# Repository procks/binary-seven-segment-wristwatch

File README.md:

# binary-seven-segment-wristwatch
A minimalist binary wristwatch that tells time using a 7-segment display

[Video](https://www.youtube.com/watch?v=ZBKZWdPcJMU)

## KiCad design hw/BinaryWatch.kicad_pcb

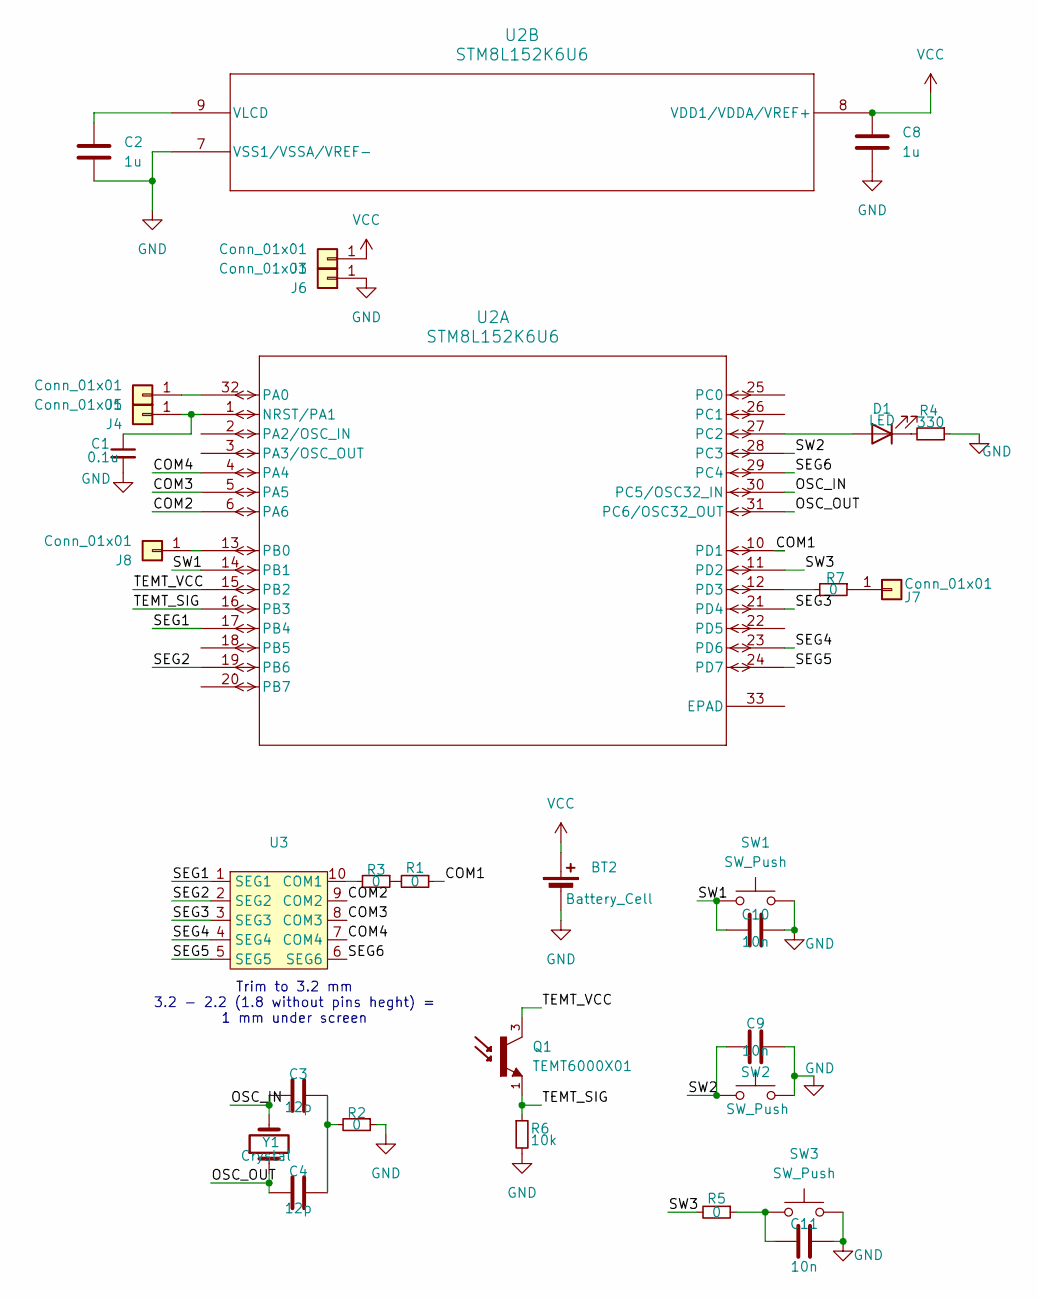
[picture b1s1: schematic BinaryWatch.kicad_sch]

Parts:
BT2: Battery_Cell; BatteryHolder_MYOUNG_BS-07-A1BJ001_CR2032
C1: 0.1u; C_0603_1608Metric
C2: 1u; C_0603_1608Metric
C3, C4: 12p; Fuse_0402_1005Metric
C8: 1u; Fuse_0402_1005Metric
C9, C10, C11: 10n; Fuse_0402_1005Metric
D1: LED; LED_0603_1608Metric
J3, J4, J5, J6, J7, J8: Conn_01x01; SolderWirePad_1x01_SMD_1x2mm
Q1: TEMT6000X01; TRANS_TEMT6000X01; PARTREV 1.9
R1, R2, R3, R5: 0; R_0603_1608Metric
R4: 330; R_0402_1005Metric
R6: 10k; R_0402_1005Metric
R7: 0; R_0402_1005Metric
SW1, SW2: SW_Push; SW_SPST_EVQP7A
SW3: SW_Push; SW_Push_SPST_NO_Alps_SKRK
U2: STM8L152K6U6; UFQFPN32-5x5mm-L
U3: 3SegLCD10Pin
Y1: Crystal; Crystal_SMD_2012-2Pin_2.0x1.2mm

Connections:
/COM1: R1.1, U2.10 (PD1)
/COM2: U2.6 (PA6), U3.9 (COM2)
/COM3: U2.5 (PA5), U3.8 (COM3)
/COM4: U2.4 (PA4), U3.7 (COM4)
/OSC_IN: C3.2, U2.30 (PC5/OSC32_IN), Y1.2
/OSC_OUT: C4.1, U2.31 (PC6/OSC32_OUT), Y1.1
/SEG1: U2.17 (PB4), U3.1 (SEG1)
/SEG2: U2.19 (PB6), U3.2 (SEG2)
/SEG3: U2.21 (PD4), U3.3 (SEG3)
/SEG4: U2.23 (PD6), U3.4 (SEG4)
/SEG5: U2.24 (PD7), U3.5 (SEG5)
/SEG6: U2.29 (PC4), U3.6 (SEG6)
/SW1: C10.1, SW1.1, U2.14 (PB1)
/SW2: C9.1, SW2.1, U2.28 (PC3)
/SW3: R5.2, U2.11 (PD2)
/TEMT_SIG: Q1.1, R6.1, U2.16 (PB3)
/TEMT_VCC: Q1.3, U2.15 (PB2)
GND: BT2.2 (-), C1.2, C2.2, C8.1, C9.2, C10.2, C11.2, J6.1, R2.1, R4.1, R6.2, SW1.2, SW2.2, SW3.2, U2.7 (VSS1/VSSA/VREF-)
unnamed: C3.1, C4.2, R2.2
unnamed: C11.1, R5.1, SW3.1
unnamed: D1.2 (A), U2.27 (PC2)
unnamed: D1.1 (K), R4.2
unnamed: C1.1, J4.1, U2.1 (NRST/PA1)
unnamed: J5.1, U2.32 (PA0)
unnamed: J7.1, R7.1
unnamed: J8.1, U2.13 (PB0)
unnamed: R1.2, R3.1
unnamed: R7.2, U2.12 (PD3)
unnamed: C2.1, U2.9 (VLCD)
unnamed: R3.2, U3.10 (COM1)
VCC: BT2.1 (+), C8.2, J3.1, U2.8 (VDD1/VDDA/VREF+)

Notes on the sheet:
Trim to 3.2 mm 3.2 - 2.2 (1.8 without pins heght) = 1 mm under screen

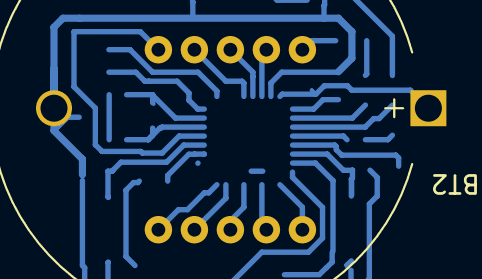
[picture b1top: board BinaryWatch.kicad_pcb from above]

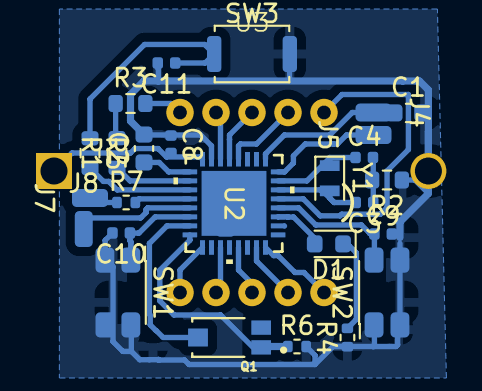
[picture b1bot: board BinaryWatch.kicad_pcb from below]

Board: 2 copper layers, 28 parts (27 on the bottom side), 31 nets.

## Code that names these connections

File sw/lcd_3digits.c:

#include "lcd_3digits.h"

void setDigitSegments(const uint8_t active[7], uint8_t position);

#define DIGIT_N 13
const uint8_t numberSegments[DIGIT_N][7] = {
    // Segments for digits 0-9 (A, B, C, D, E, F, G)
    {1,1,1,1,1,1,0}, // 0
    {0,1,1,0,0,0,0}, // 1
    {1,1,0,1,1,0,1}, // 2
    {1,1,1,1,0,0,1}, // 3
    {0,1,1,0,0,1,1}, // 4
    {1,0,1,1,0,1,1}, // 5
    {1,0,1,1,1,1,1}, // 6
    {1,1,1,0,0,0,0}, // 7
    {1,1,1,1,1,1,1}, // 8
    {1,1,1,1,0,1,1}, // 9
    {1,1,1,1,1,0,0}, // 10
    {0,1,1,0,0,1,0}, // 11
    {1,1,0,1,1,1,1}, // 12
};

const uint8_t emptySegments[DIGIT_N] = {0, 0, 0, 0, 0, 0, 0};  // empty
const uint8_t bitZeroSegments[DIGIT_N] = {0, 0, 0, 0, 0, 0, 1};  // -

static uint8_t activeBits[7];

const uint8_t digit0Segments[7][2] = {
  {2, 0x20}, //A
  {6, 0x02}, //B
  {9, 0x20}, //C
  {13, 0x10}, //D
  {10, 0x01}, //E
  {3, 0x01}, //F
  {6, 0x10}, //G
};

const uint8_t digit1Segments[7][2] = {
  {2, 0x04}, //A
  {5, 0x40}, //B
  {9, 0x04}, //C
  {13, 0x01}, //D
  {9, 0x10}, //E
  {2, 0x10}, //F
  {6, 0x01}, //G
};

const uint8_t digit2Segments[7][2] = {
  {1, 0x40}, //A
  {5, 0x04}, //B
  {8, 0x40}, //C
  {12, 0x10}, //D
  {9, 0x01}, //E
  {2, 0x01}, //F
  {5, 0x10}, //G
};

//Seg1 PB4 SEG14
//Seg2 PB6 SEG16
//Seg3 PD4 SEG18
//Seg4 PD6 SEG20
//Seg5 PD7 SEG21
//Seg6 PC4 SEG24
  
// 28 bit
//example segment 14 com 1: 1 * 28 + 14 = 42;  RAM[42 / 8] = 1 << 42 % 8  //   LCD->RAM[5] |= 0x04
// https://pl.kotl.in/D8QqgNEhd
// https://pl.kotl.in/o2Y2ADsXu
//    val segments = listOf(14, 16, 18, 20, 21, 24)
//    segments.forEach { seg ->
//        for (com in 0..3) {
//                val bitsn = com * 28 + seg
//                val ramIndex = bitsn / 8
//                val bit = bitsn % 8
//                val mask = 1 shl bit
//                //println("LCD->RAM[$ramIndex] |= 0x${mask.toString(16).padStart(2, '0').uppercase()}; // SEG$seg COM$com")
//                println("{$ramIndex, 0x${mask.toString(16).padStart(2, '0').uppercase()}},")
//        }
//    }

//LCD->RAM[1] |= 0x40; // SEG14 COM0 // 3A
//LCD->RAM[5] |= 0x04; // SEG14 COM1 // 3B
//LCD->RAM[8] |= 0x40; // SEG14 COM2 // 3C
////LCD->RAM[12] |= 0x04; // SEG14 COM3 // nc
//LCD->RAM[2] |= 0x01; // SEG16 COM0 // 3F
//LCD->RAM[5] |= 0x10; // SEG16 COM1 // 3G
//LCD->RAM[9] |= 0x01; // SEG16 COM2 // 3E
//LCD->RAM[12] |= 0x10; // SEG16 COM3 // 3D
    
//LCD->RAM[2] |= 0x04; // SEG18 COM0 // 2A
//LCD->RAM[5] |= 0x40; // SEG18 COM1 // 2B
//LCD->RAM[9] |= 0x04; // SEG18 COM2 // 2C
////LCD->RAM[12] |= 0x40; // SEG18 COM3 // nc
//LCD->RAM[2] |= 0x10; // SEG20 COM0 // 2F
//LCD->RAM[6] |= 0x01; // SEG20 COM1 // 2G
//LCD->RAM[9] |= 0x10; // SEG20 COM2 // 2E
//LCD->RAM[13] |= 0x01; // SEG20 COM3 // 2D
    
//LCD->RAM[2] |= 0x20; // SEG21 COM0 // 1A
//LCD->RAM[6] |= 0x02; // SEG21 COM1 // 1B
//LCD->RAM[9] |= 0x20; // SEG21 COM2 // 1C
////LCD->RAM[13] |= 0x02; // SEG21 COM3 // nc
//LCD->RAM[3] |= 0x01; // SEG24 COM0 // 1F
//LCD->RAM[6] |= 0x10; // SEG24 COM1 // 1G
//LCD->RAM[10] |= 0x01; // SEG24 COM2 // 1E
//LCD->RAM[13] |= 0x10; // SEG24 COM3 // 1D

const uint8_t *digitSegmentMappings[] = {
    (const uint8_t *)digit0Segments,
    (const uint8_t *)digit1Segments,
    (const uint8_t *)digit2Segments
};

void setDigitSegments(const uint8_t active[7], uint8_t position) {
    const uint8_t (*segments)[2] = (const uint8_t (*)[2])digitSegmentMappings[position];

    for (int i = 0; i < 7; i++) {
        if (active[i]) {
            LCD->RAM[segments[i][0]] |= segments[i][1];
        } else {
            LCD->RAM[segments[i][0]] &= ~segments[i][1];
        }
    }
}

void LCD_WriteInt(uint32_t value) {
    const uint8_t num_digits = 3;
    for (int i = num_digits - 1; i >= 0; i--) {
        if (value != 0 || i == num_digits - 1) {
            setDigitSegments(numberSegments[value % 10], i);
            value /= 10;
        } else {
            setDigitSegments(emptySegments, i);
        }
    }
}

void LCD_WriteIntPos(uint8_t value, uint8_t position) {
    setDigitSegments(numberSegments[value], position);
}

void LCD_WriteBin(uint8_t value, uint8_t position) {
    if (value == 0) {
        setDigitSegments(bitZeroSegments, position);
    } else {
        activeBits[0] = (value >> 5) & 1;  // Directly assign bit 5 to index 0

        for (int i = 0; i < 5; i++) {
            //activeBits[i] = (value >> i) & 1;
            activeBits[i + 1] = (value >> i) & 1;
        }

        setDigitSegments(activeBits, position);
    }
}
